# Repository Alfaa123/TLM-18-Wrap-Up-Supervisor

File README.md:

# TLM-18-Wrap-Up-Supervisor
A monitor system to keep track of the number of consecutive 'wraps' the azimuth axis of the TLM-18 radio telescope has completed.

# This project is in progress, the following plan is being implemented:

A standard industrial quadrature encoder is attached to the selsyn shaft to monitor the position of the selsyn pinion.

400 pulses per revolution read in quadrature would give us 1600 PPR (0.225°) resolution at the selsyn pinion. The actual angular resolution of the azimuth axis would be further multiplied by the gear ratio of the pinion and ring gear.

A standard microcontroller would be used to read the quadrature outputs of the encoder and internally keep track of the position. A standard communications link (RS-232 or similar) would be used to communicate the current position back to the computer at specified intervals.

In order to keep track of the position of the telescope during power loss, a small battery backup system will be used to maintain power to the microcontroller during all conditions. Due to the minimal power consumption of the microcontroller/encoder combination, a small lead acid deep cycle battery should be able to maintain power to that system for many hours.

An additional feature that could be implemented is additional sensors to monitor environmental conditions inside the telescope. Temperature and humidity could be logged, as well as a small Inertial Measurement Unit to detect abnormal vibration in the positioning system. Additional sensing capabilities would allow a remote user to detect issues before they get too out of control.

Physically, the electronics would be mounted in a weatherproof enclosure attached somewhere near to the selsyn pinion to keep the encoder wire as short as possible.

# Electrical Design

The TLM-18 Supervisor system is controlled by an Arduino Nano as the main MCU. This was chosen for ease of software development, ubquity and cost.

The entire system is powered by a small 12v lead acid battery float charger connected to a standard 12v UPS battery. This gives the system a short battery backup supply should mains power be inturrupted.

Attached to the Arduino is an LS7366R SPI Encoder Counter to keep track of the encoder pulses. This will allow high PPR encoders without overwhelming the inturrupt capability of the Arduino at high speeds.

A ADM488ANZ RS-422 transceiver is also attached to allow long distance and isolated communication with the TLM-18 control computer, which will be located a significant distance away and may not be at the same ground potential.

The schematic and board layout are shown below:

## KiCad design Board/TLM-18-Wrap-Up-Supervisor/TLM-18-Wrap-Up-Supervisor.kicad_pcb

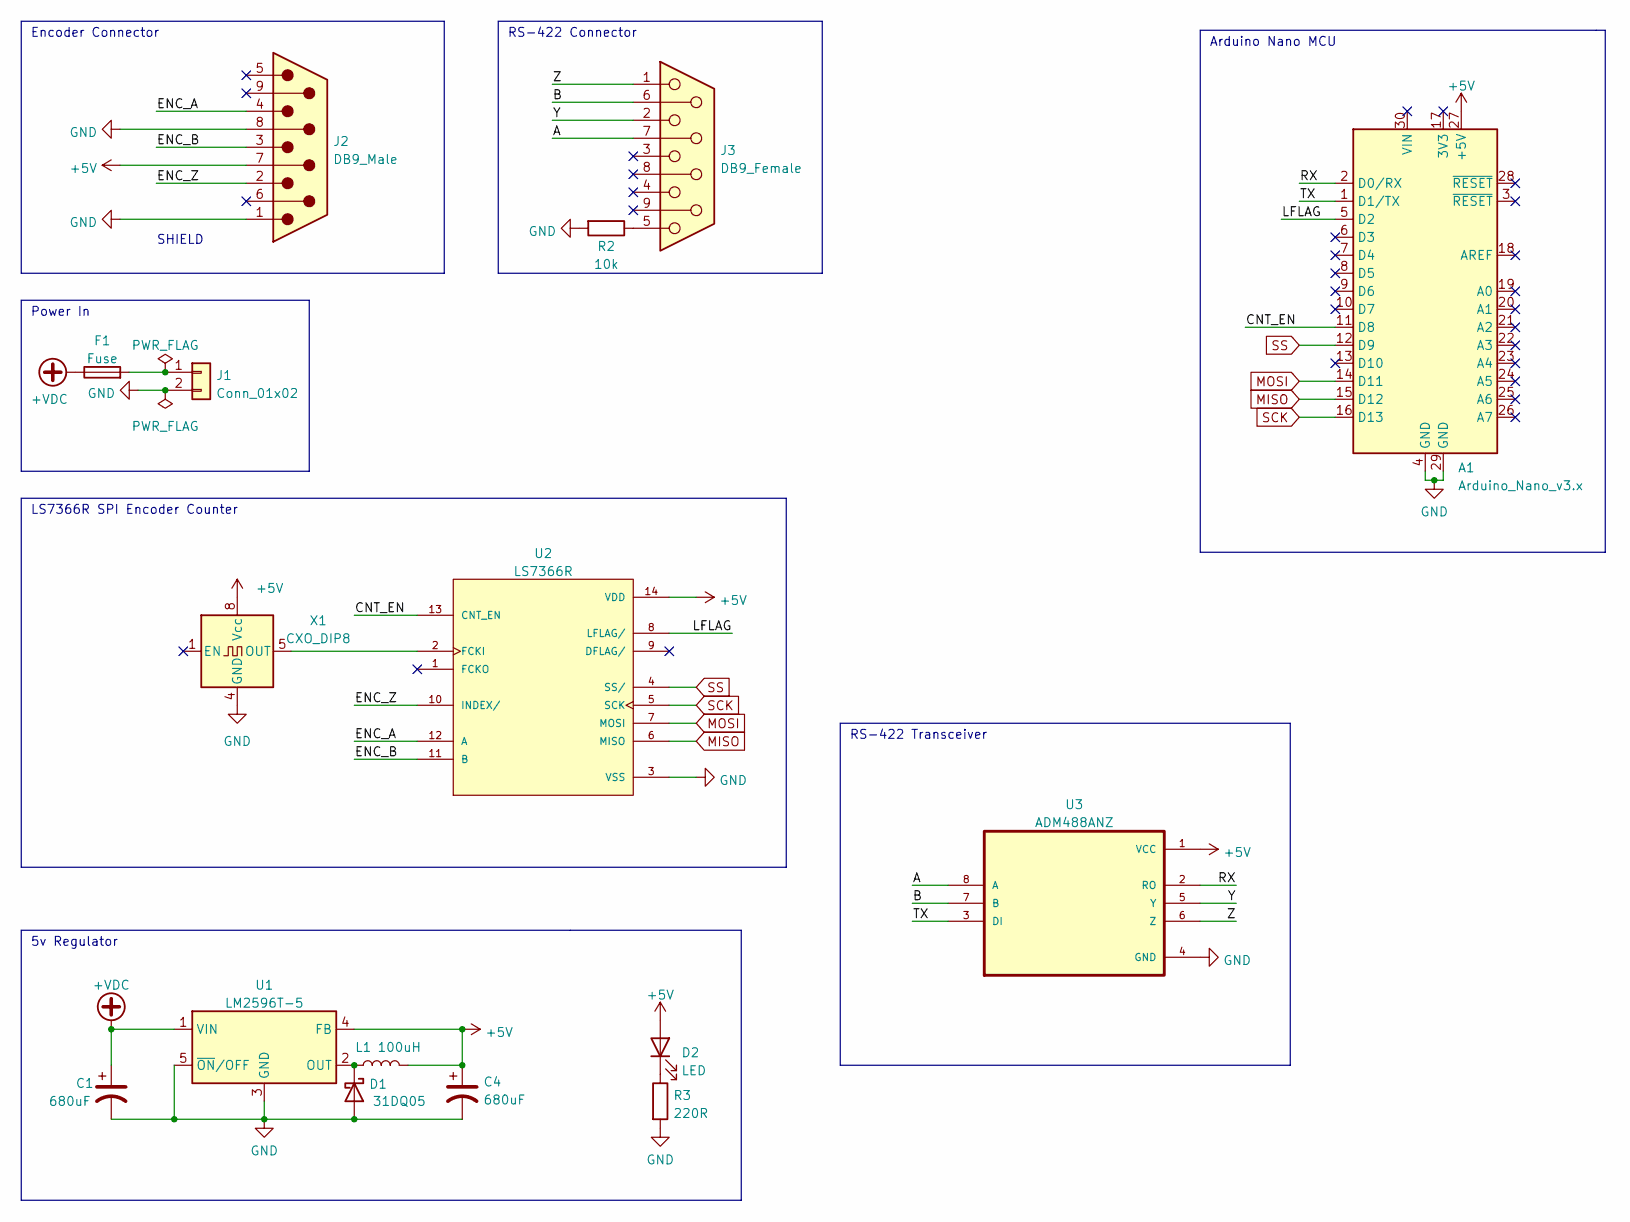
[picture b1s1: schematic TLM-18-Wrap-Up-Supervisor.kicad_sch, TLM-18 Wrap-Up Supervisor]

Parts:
A1: Arduino_Nano_v3.x; Arduino_Nano
C1, C4: 680uF; C_Radial_D12.5mm_H20.0mm_P5.00mm
D1: 31DQ05; D_DO-201AD_P15.24mm_Horizontal
D2: LED; LED_D5.0mm
F1: Fuse; Fuseholder_Blade_Mini_Keystone_3568
J1: Conn_01x02; PinHeader_1x02_P2.54mm_Vertical
J2: DB9_Male; DSUB-9_Male_Vertical_P2.77x2.84mm_MountingHoles
J3: DB9_Female; DSUB-9_Female_Vertical_P2.77x2.84mm_MountingHoles
L1: 100uH; L_Radial_D12.0mm_P5.00mm_Fastron_11P
R2: 10k; R_Axial_DIN0207_L6.3mm_D2.5mm_P7.62mm_Horizontal
R3: 220R; R_Axial_DIN0207_L6.3mm_D2.5mm_P7.62mm_Horizontal
U1: LM2596T-5; TO-220-5_P3.4x3.7mm_StaggerOdd_Lead3.8mm_Vertical
U2: LS7366R; DIP762W45P254L1917H533Q14; PARTREV June 2014
U3: ADM488ANZ; DIP787W46P254L953H457Q8
X1: CXO_DIP8; Oscillator_DIP-8

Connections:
+5V: A1.27 (+5V), C4.1, D2.2 (A), J2.7, L1.2, U1.4 (FB), U2.14 (VDD), U3.1 (VCC), X1.8 (Vcc)
+VDC: C1.1, F1.1, U1.1 (VIN)
/A: J3.7, U3.8 (A)
/B: J3.6, U3.7 (B)
/CNT_EN: A1.11 (D8), U2.13 (CNT_EN)
/ENC_A: J2.4, U2.12 (A)
/ENC_B: J2.3, U2.11 (B)
/ENC_Z: J2.2, U2.10 (INDEX/)
/LFLAG: A1.5 (D2), U2.8 (LFLAG/)
/RX: A1.2 (D0/RX), U3.2 (RO)
/TX: A1.1 (D1/TX), U3.3 (DI)
/Y: J3.2, U3.5 (Y)
/Z: J3.1, U3.6 (Z)
GND: A1.4 (GND), A1.29 (GND), C1.2, C4.2, D1.2 (A), J1.2, J2.1, J2.8, R2.2, R3.2, U1.3 (GND), U1.5 (~ON/OFF), U2.3 (VSS), U3.4 (GND), X1.4 (GND)
MISO: A1.15 (D12), U2.6 (MISO)
MOSI: A1.14 (D11), U2.7 (MOSI)
unnamed: D1.1 (K), L1.1, U1.2 (OUT)
unnamed: D2.1 (K), R3.1
unnamed: F1.2, J1.1
unnamed: J3.5, R2.1
unnamed: U2.2 (FCKI), X1.5 (OUT)
SCK: A1.16 (D13), U2.5 (SCK)
SS: A1.12 (D9), U2.4 (SS/)

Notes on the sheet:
RS-422 Connector
Arduino Nano MCU
LS7366R SPI Encoder Counter
Power In
Encoder Connector
SHIELD
RS-422 Transceiver
5v Regulator

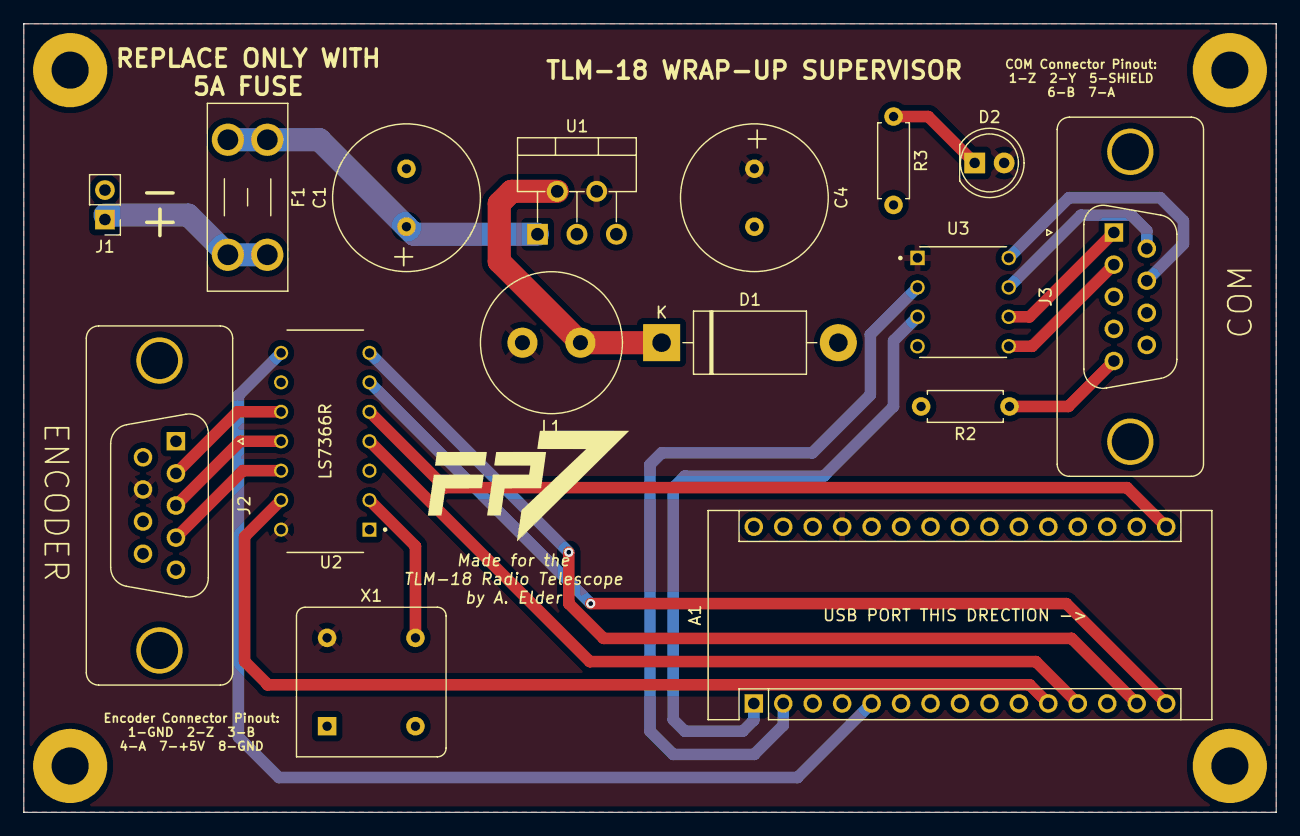
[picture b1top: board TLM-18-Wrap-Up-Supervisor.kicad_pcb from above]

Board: 2 copper layers, 108.0 x 68.0 mm, 16 parts (0 on the bottom side), 23 nets.

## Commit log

2022-05-15 Version 1 of the Schematic Finished
2022-05-15 Add photos... update readme
2022-06-18 Added photos, finished board layout, updated readme
2022-08-25 Updated board SS + BOM
    Changed crystal to prepackaged oscillator, added extra silkscreen marks
